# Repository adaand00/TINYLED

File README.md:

# TINYLED

Light-up sign with an attiny10 and three ws2812b RGB LEDs. 

## Introduction

This is a simple project to make a light-up stand for laser-cut acrylic signs. I mainly did this as an excercise in using the attiny10-series of microcontrollers. They are very limited with just 512 or 1024 bytes of flash and 32 bytes RAM. The final code is just under 500 bytes, of which half is for driving the LEDs. 

## Circuit board

The PCB was designed in fusion360. There are test points on the underside for pogo-pin programming. The PCB also has slots for the laser cut feet to snap-fit into. 

Gerber files are supplied in the hardware folder. 

## Programming

I used the [Attiny10IDE](https://github.com/wholder/ATTiny10IDE) by @wholder to program the chip. I managed to fit one rainbow animation and a couple solid color animations into the 512 byte memory of the attiny5. Because of space constraints, I have only implemented hue control for the LEDs. If the code was optimized a bit, brightness control could perhaps also be implemented, which would enable some more cool animations. 

The source code is provided as a .c file that can be modified and built with the attiny10IDE. There is also a .ino file that can be used to turn an arduino into a programmer.

## BOM

* 1x Attiny4/5/9/10 (tested with 5, should work with all)
* 3x ws2812b, also known as neopixels
* 1x 6x6mm tactile pushbutton with SMD mounting
* 1x 500 ohm 0603 resistor
* 1x molex 105017-0001 micro USB connector 
* 1x PCB 

## Future work

- [ ] Add brightness control in LED driver function.
- [ ] Modify PCB to allow for bigger signs (Move feet, add more LEDs, use smaller switch).
- [ ] Ditch micro USB for battery, USB-C or barrel jack.

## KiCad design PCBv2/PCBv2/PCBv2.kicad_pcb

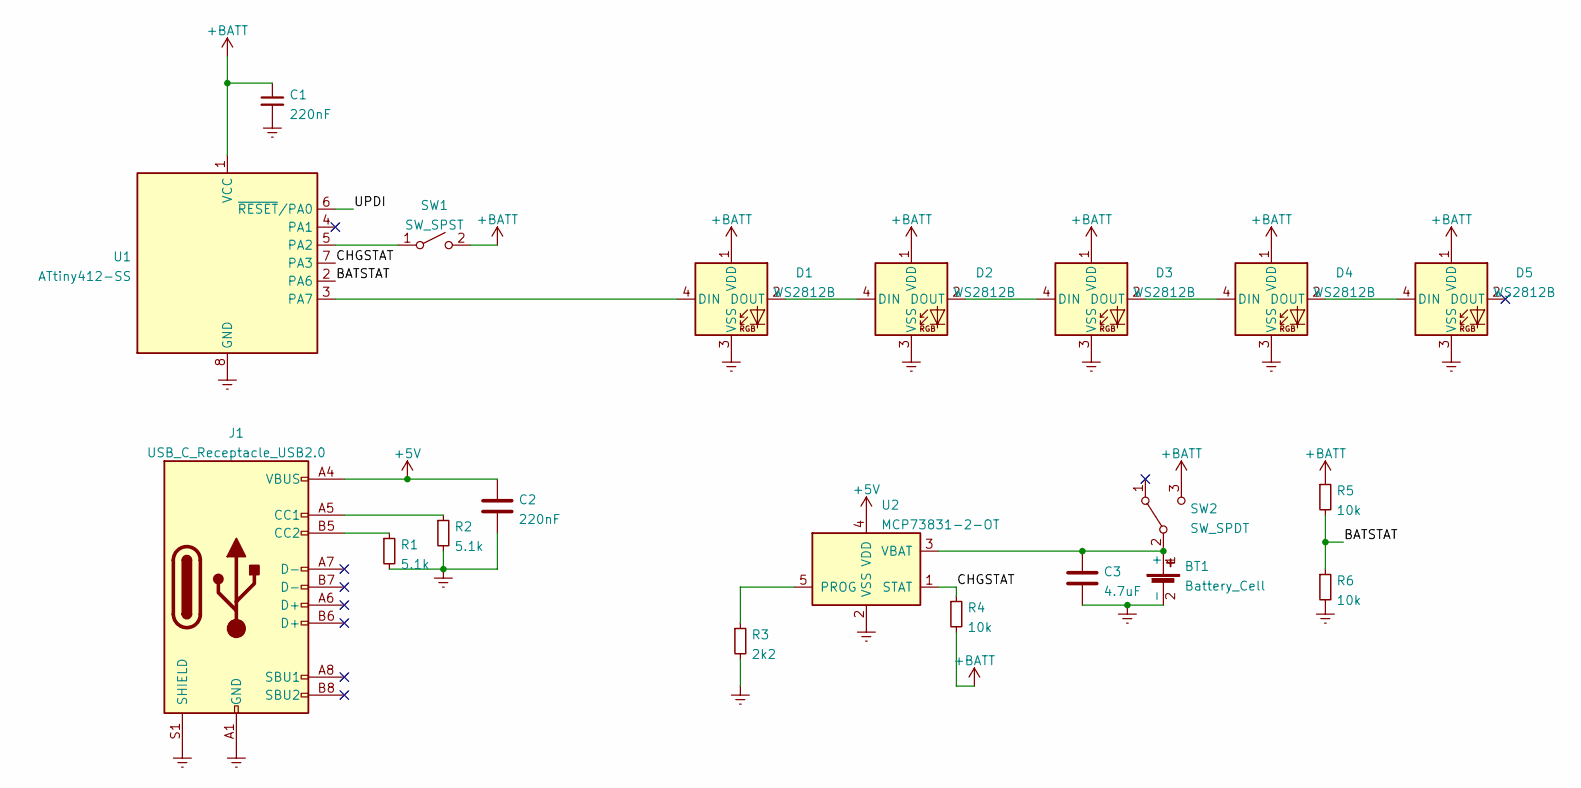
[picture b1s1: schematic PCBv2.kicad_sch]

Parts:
BT1: Battery_Cell; CB-18650-PC2
C1, C2: 220nF; C_0603_1608Metric_Pad1.08x0.95mm_HandSolder
C3: 4.7uF; C_1206_3216Metric_Pad1.33x1.80mm_HandSolder
D1, D2, D3, D4, D5: WS2812B; LED_WS2812B_PLCC4_5.0x5.0mm_P3.2mm
J1: USB_C_Receptacle_USB2.0; USB_C_Receptacle_HRO_TYPE-C-31-M-12
R1, R2: 5.1k; R_0603_1608Metric_Pad0.98x0.95mm_HandSolder
R3: 2k2; R_0603_1608Metric_Pad0.98x0.95mm_HandSolder
R4, R5, R6: 10k; R_0603_1608Metric_Pad0.98x0.95mm_HandSolder
SW1: SW_SPST; SW_Push_1P1T_NO_6x6mm_H9.5mm
SW2: SW_SPDT; SW_SPDT_CK-JS102011SAQN
U1: ATtiny412-SS; SOIC-8_3.9x4.9mm_P1.27mm
U2: MCP73831-2-OT; SOT-23-5

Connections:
+5V: C2.1, J1.A4 (VBUS), J1.A9 (VBUS), J1.B4 (VBUS), J1.B9 (VBUS), U2.4 (VDD)
+BATT: C1.1, D1.1 (VDD), D2.1 (VDD), D3.1 (VDD), D4.1 (VDD), D5.1 (VDD), R4.2, R5.1, SW1.2 (B), SW2.3 (C), U1.1 (VCC)
/BATSTAT: R5.2, R6.1, U1.2 (PA6)
/CHGSTAT: R4.1, U1.7 (PA3), U2.1 (STAT)
/UPDI: U1.6 (~RESET/PA0)
Earth: BT1.2 (-), C1.2, C2.2, C3.2, D1.3 (VSS), D2.3 (VSS), D3.3 (VSS), D4.3 (VSS), D5.3 (VSS), J1.A1 (GND), J1.A12 (GND), J1.B1 (GND), J1.B12 (GND), J1.S1 (SHIELD), R1.2, R2.2, R3.2, R6.2, U1.8 (GND), U2.2 (VSS)
unnamed: BT1.1 (+), C3.1, SW2.2 (B), U2.3 (VBAT)
unnamed: D1.2 (DOUT), D2.4 (DIN)
unnamed: D1.4 (DIN), U1.3 (PA7)
unnamed: D2.2 (DOUT), D3.4 (DIN)
unnamed: D3.2 (DOUT), D4.4 (DIN)
unnamed: D4.2 (DOUT), D5.4 (DIN)
unnamed: J1.A5 (CC1), R2.1
unnamed: J1.B5 (CC2), R1.1
unnamed: R3.1, U2.5 (PROG)
unnamed: SW1.1 (A), U1.5 (PA2)

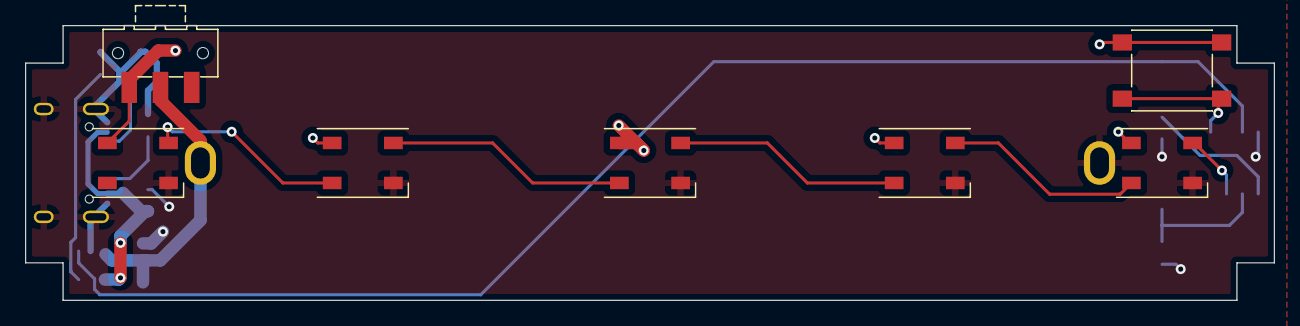
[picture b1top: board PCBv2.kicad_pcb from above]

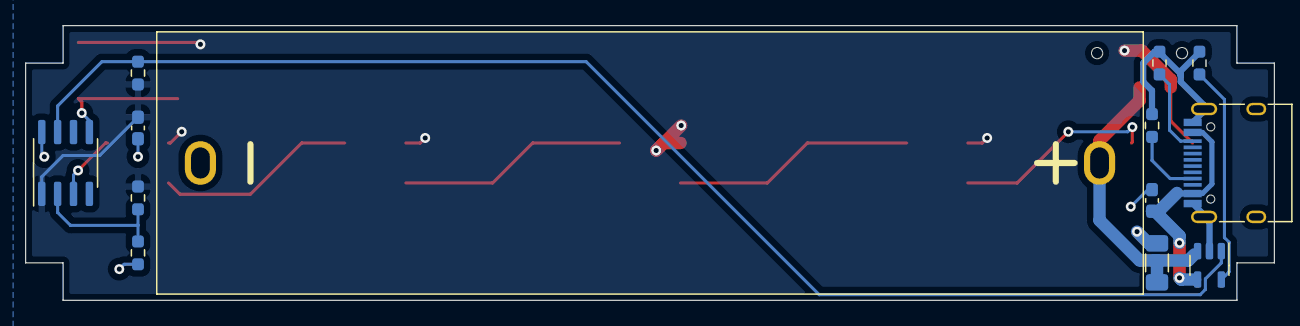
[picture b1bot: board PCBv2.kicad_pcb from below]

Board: 2 copper layers, 100.0 x 22.0 mm, 20 parts (13 on the bottom side), 15 nets.

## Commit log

2021-04-18 Added project files
2021-04-18 Added images of PCB
2021-04-18 Create LICENSE
2022-06-15 update gitignore
2022-06-15 start on PCB v2
2022-12-01 v2 Updates, not tested yet
